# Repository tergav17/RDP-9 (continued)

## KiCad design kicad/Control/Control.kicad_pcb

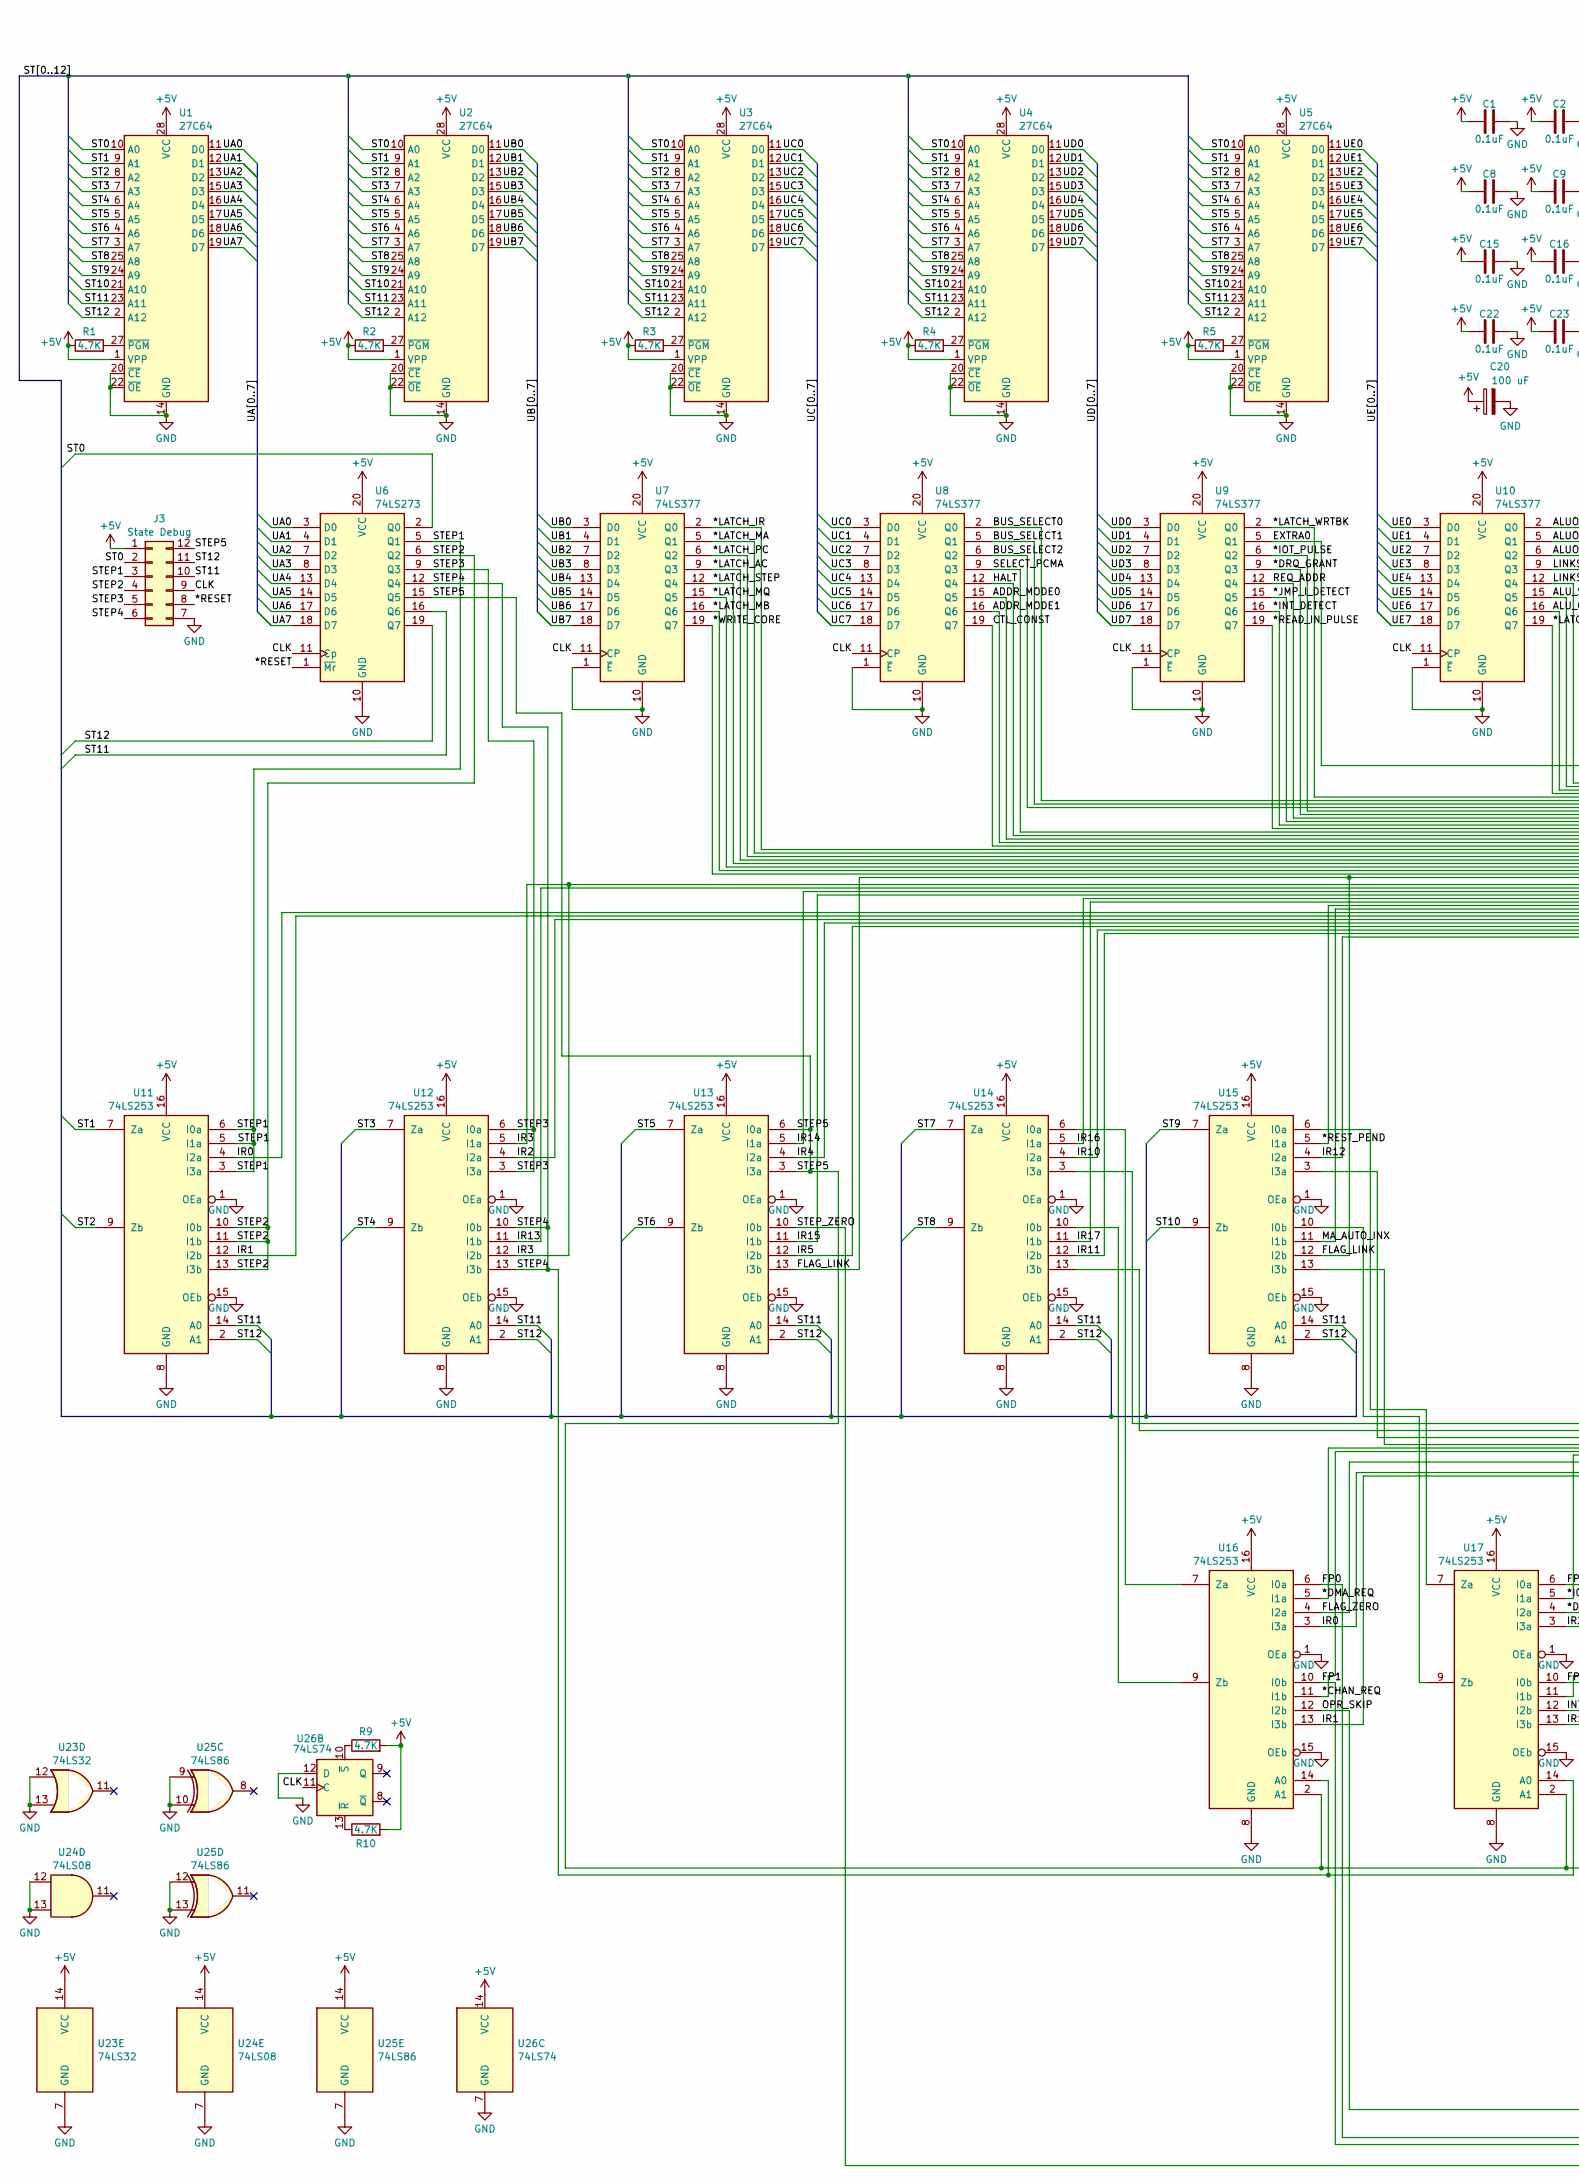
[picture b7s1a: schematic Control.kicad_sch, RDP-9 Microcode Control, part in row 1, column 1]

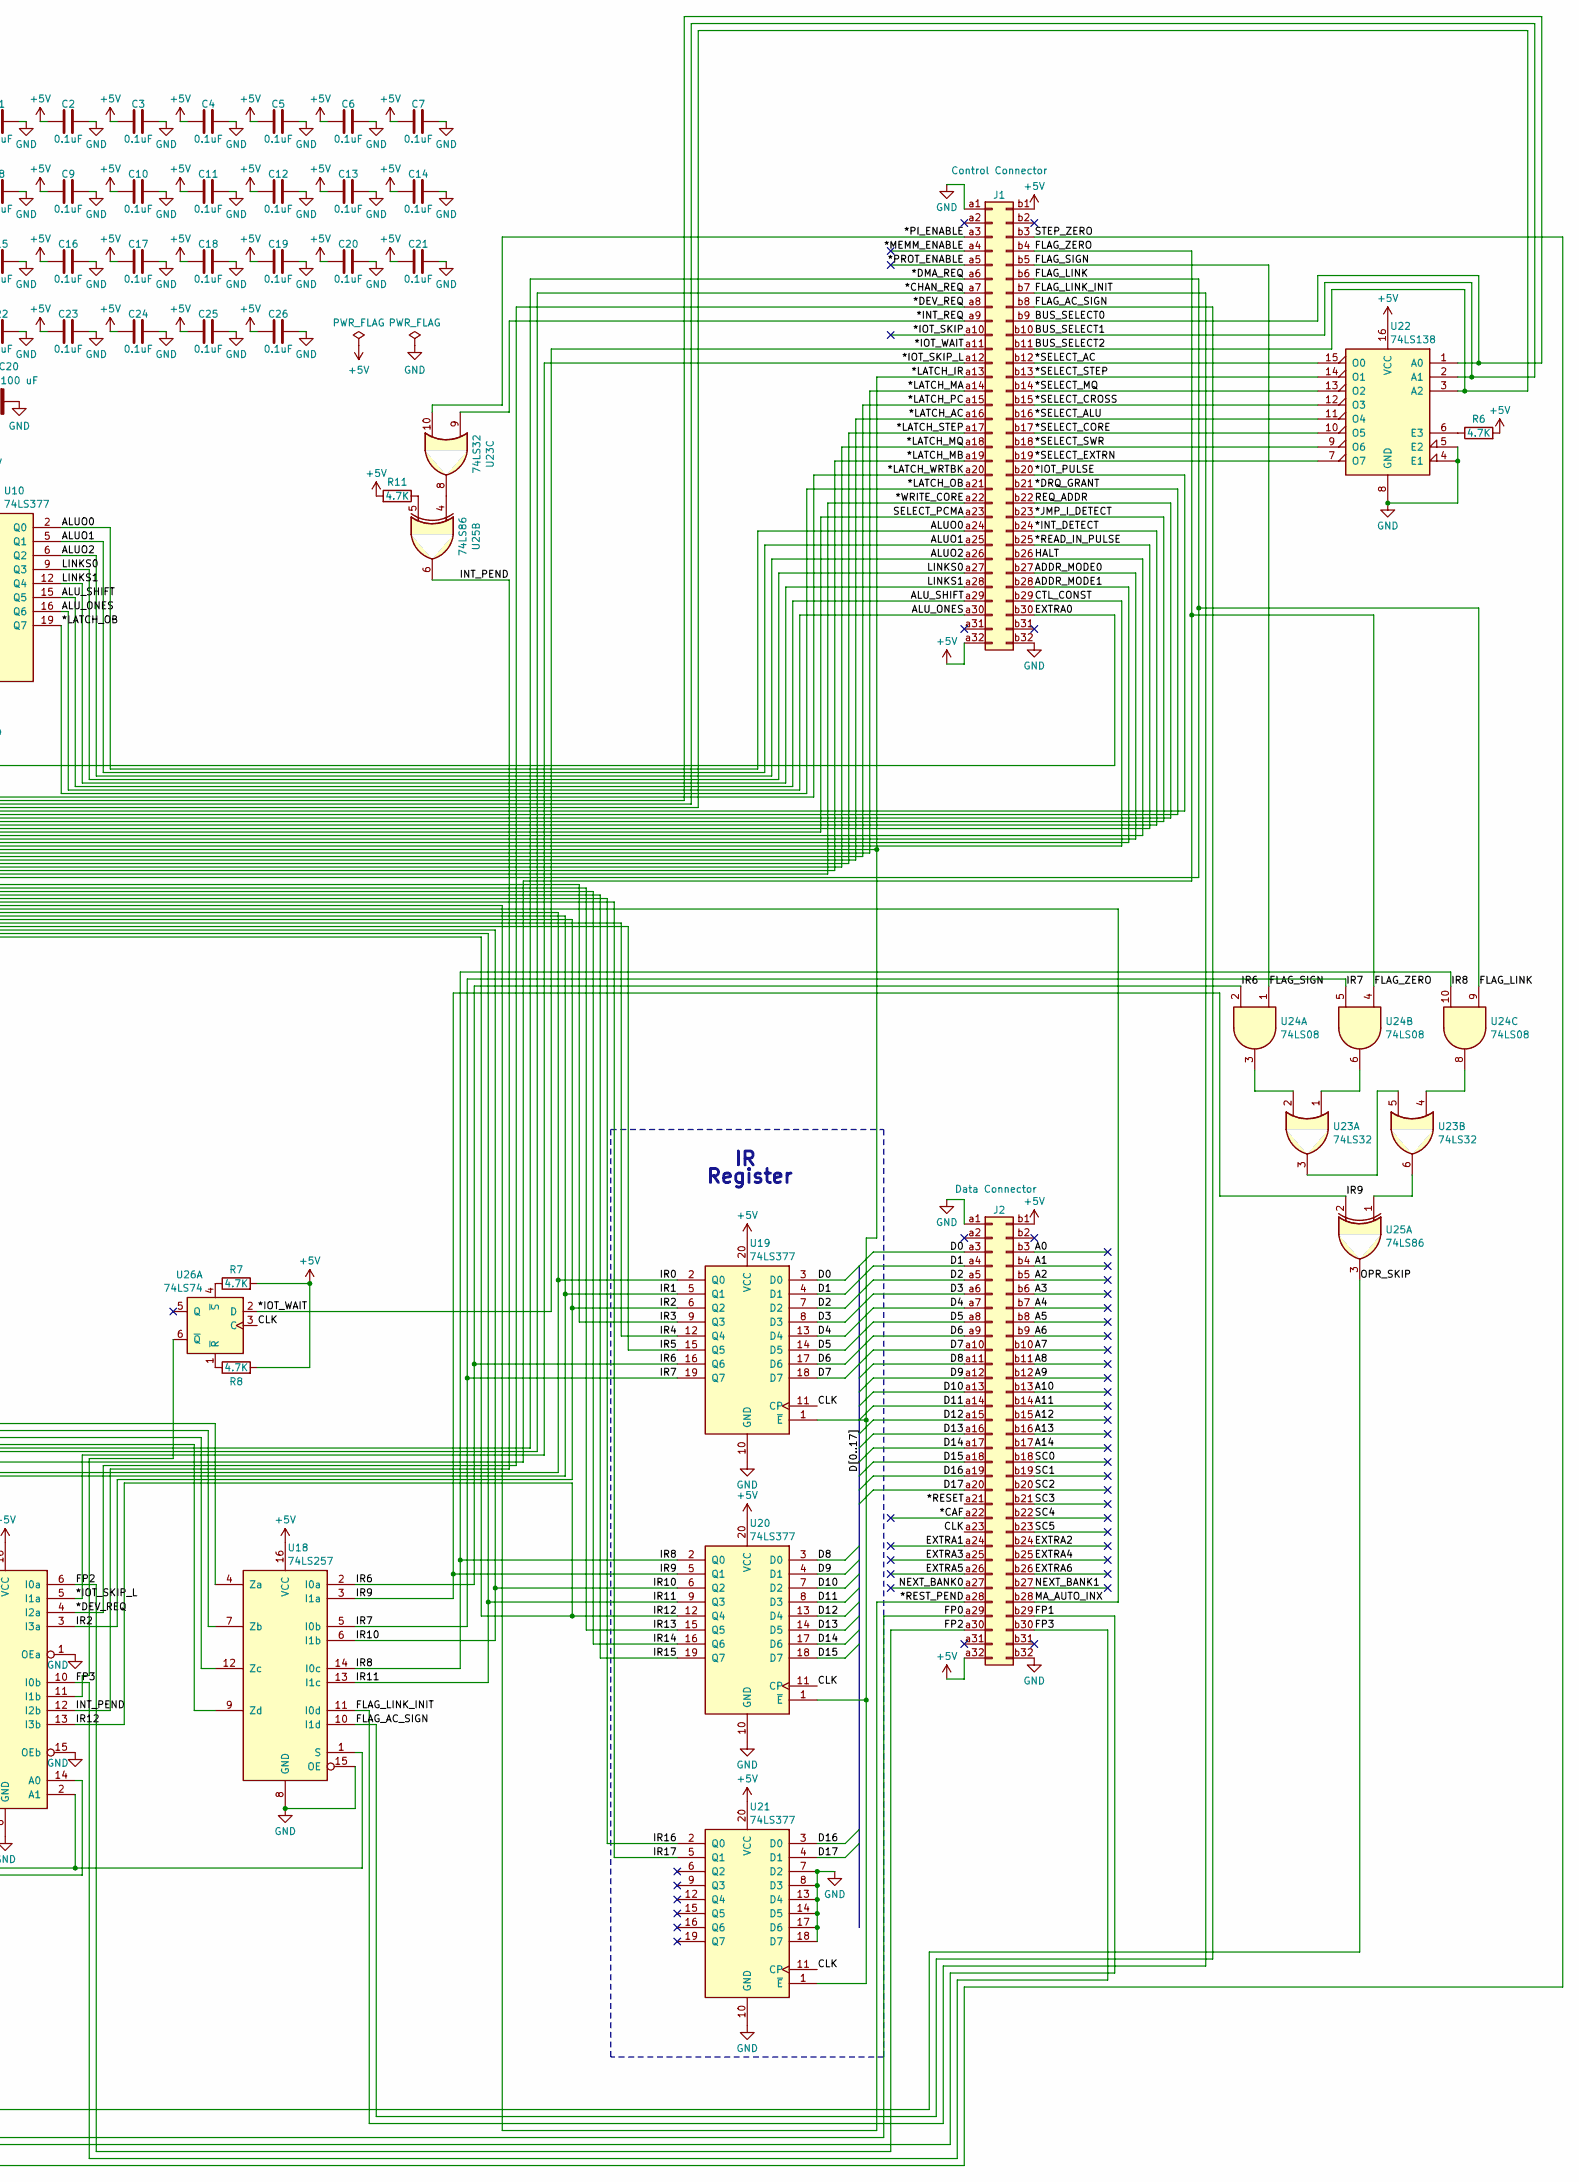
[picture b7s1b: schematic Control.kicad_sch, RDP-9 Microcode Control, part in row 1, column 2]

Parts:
C1, C2, C3, C4, C5, C6, C7, C8, C9, C10, C11, C12, C13, C14, C15, C16, C17, C18, C19, C21, C22, C23, C24, C25, C26: 0.1uF; C_Disc_D5.0mm_W2.5mm_P5.00mm
C20: 100 uF; CP_Radial_D6.3mm_P2.50mm
J1: Control Connector; DIN41612_B_2x32_Male_Horizontal_THT
J2: Data Connector; DIN41612_B_2x32_Male_Horizontal_THT
J3: State Debug; IDC-Header_2x06_P2.54mm_Horizontal
R1, R2, R3, R4, R5, R6, R7, R8, R9, R10, R11: 4.7K; R_Axial_DIN0207_L6.3mm_D2.5mm_P7.62mm_Horizontal
U1, U2, U3, U4, U5: 27C64; DIP-28_W15.24mm
U6: 74LS273; DIP-20_W7.62mm
U7, U8, U9, U10, U19, U20, U21: 74LS377; DIP-20_W7.62mm
U11, U12, U13, U14, U15, U16, U17: 74LS253; DIP-16_W7.62mm
U18: 74LS257; DIP-16_W7.62mm
U22: 74LS138; DIP-16_W7.62mm
U23: 74LS32; DIP-14_W7.62mm
U24: 74LS08; DIP-14_W7.62mm
U25: 74LS86; DIP-14_W7.62mm
U26: 74LS74; DIP-14_W7.62mm

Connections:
+5V: C1.1, C2.1, C3.1, C4.1, C5.1, C6.1, C7.1, C8.1, C9.1, C10.1, C11.1, C12.1, C13.1, C14.1, C15.1, C16.1, C17.1, C18.1, C19.1, C20.1, C21.1, C22.1, C23.1, C24.1, C25.1, C26.1, J1.a32, J1.b1, J2.a32, J2.b1, J3.1, R1.1, R2.1, R3.1, R4.1, R5.1, R6.2, R7.2, R8.2, R9.2, R10.2, R11.2, U1.1 (VPP), U1.28 (VCC), U2.1 (VPP), U2.28 (VCC), U3.1 (VPP), U3.28 (VCC), U4.1 (VPP), U4.28 (VCC), U5.1 (VPP), U5.28 (VCC), U6.20 (VCC), U7.20 (VCC), U8.20 (VCC), U9.20 (VCC), U10.20 (VCC), U11.16 (VCC), U12.16 (VCC), U13.16 (VCC), U14.16 (VCC), U15.16 (VCC), U16.16 (VCC), U17.16 (VCC), U18.16 (VCC), U19.20 (VCC), U20.20 (VCC), U21.20 (VCC), U22.16 (VCC), U23.14 (VCC), U24.14 (VCC), U25.14 (VCC), U26.14 (VCC); also elsewhere on the board
/*CAF: J2.a22
/*CHAN_REQ: J1.a7, U16.11 (I1b)
/*DEV_REQ: J1.a8, U17.4 (I2a)
/*DMA_REQ: J1.a6, U16.5 (I1a)
/*DRQ_GRANT: J1.b21, U9.9 (Q3)
/*INT_DETECT: J1.b24, U9.16 (Q6)
/*INT_REQ: J1.a9, U23.9
/*IOT_PULSE: J1.b20, U9.6 (Q2)
/*IOT_SKIP: J1.a10
/*IOT_SKIP_L: J1.a12, U17.5 (I1a)
/*IOT_WAIT: J1.a11, U26.2 (D)
/*JMP_I_DETECT: J1.b23, U9.15 (Q5)
/*LATCH_AC: J1.a16, U7.9 (Q3)
/*LATCH_IR: J1.a13, U7.2 (Q0), U19.1 (~E), U20.1 (~E), U21.1 (~E)
/*LATCH_MA: J1.a14, U7.5 (Q1)
/*LATCH_MB: J1.a19, U7.16 (Q6)
/*LATCH_MQ: J1.a18, U7.15 (Q5)
/*LATCH_OB: J1.a21, U10.19 (Q7)
/*LATCH_PC: J1.a15, U7.6 (Q2)
/*LATCH_STEP: J1.a17, U7.12 (Q4)
/*LATCH_WRTBK: J1.a20, U9.2 (Q0)
/*MEMM_ENABLE: J1.a4
/*PI_ENABLE: J1.a3, U23.10
/*PROT_ENABLE: J1.a5
/*READ_IN_PULSE: J1.b25, U9.19 (Q7)
/*RESET: J2.a21, J3.8, U6.1 (~Mr)
/*REST_PEND: J2.a28, U15.5 (I1a)
/*SELECT_AC: J1.b12, U22.15 (O0)
/*SELECT_ALU: J1.b16, U22.11 (O4)
/*SELECT_CORE: J1.b17, U22.10 (O5)
/*SELECT_CROSS: J1.b15, U22.12 (O3)
/*SELECT_EXTRN: J1.b19, U22.7 (O7)
/*SELECT_MQ: J1.b14, U22.13 (O2)
/*SELECT_STEP: J1.b13, U22.14 (O1)
/*SELECT_SWR: J1.b18, U22.9 (O6)
/*WRITE_CORE: J1.a22, U7.19 (Q7)
/A0: J2.b3
/A1: J2.b4
/A2: J2.b5
/A3: J2.b6
/A4: J2.b7
/A5: J2.b8
/A6: J2.b9
/A7: J2.b10
/A8: J2.b11
/A9: J2.b12
/A10: J2.b13
/A11: J2.b14
/A12: J2.b15
/A13: J2.b16
/A14: J2.b17
/ADDR_MODE0: J1.b27, U8.15 (Q5)
/ADDR_MODE1: J1.b28, U8.16 (Q6)
/ALUO0: J1.a24, U10.2 (Q0)
/ALUO1: J1.a25, U10.5 (Q1)
/ALUO2: J1.a26, U10.6 (Q2)
/ALU_ONES: J1.a30, U10.16 (Q6)
/ALU_SHIFT: J1.a29, U10.15 (Q5)
/BUS_SELECT0: J1.b9, U8.2 (Q0), U22.1 (A0)
/BUS_SELECT1: J1.b10, U8.5 (Q1), U22.2 (A1)
/BUS_SELECT2: J1.b11, U8.6 (Q2), U22.3 (A2)
/CLK: J2.a23, J3.9, U6.11 (Cp), U7.11 (CP), U8.11 (CP), U9.11 (CP), U10.11 (CP), U19.11 (CP), U20.11 (CP), U21.11 (CP), U26.3 (C), U26.11 (C)
/CTL_CONST: J1.b29, U8.19 (Q7)
/D0: J2.a3, U19.3 (D0)
/D1: J2.a4, U19.4 (D1)
/D2: J2.a5, U19.7 (D2)
/D3: J2.a6, U19.8 (D3)
/D4: J2.a7, U19.13 (D4)
/D5: J2.a8, U19.14 (D5)
/D6: J2.a9, U19.17 (D6)
/D7: J2.a10, U19.18 (D7)
/D8: J2.a11, U20.3 (D0)
/D9: J2.a12, U20.4 (D1)
/D10: J2.a13, U20.7 (D2)
/D11: J2.a14, U20.8 (D3)
/D12: J2.a15, U20.13 (D4)
/D13: J2.a16, U20.14 (D5)
/D14: J2.a17, U20.17 (D6)
/D15: J2.a18, U20.18 (D7)
/D16: J2.a19, U21.3 (D0)
/D17: J2.a20, U21.4 (D1)
/EXTRA0: J1.b30, U9.5 (Q1)
/EXTRA1: J2.a24
/EXTRA2: J2.b24
/EXTRA3: J2.a25
/EXTRA4: J2.b25
/EXTRA5: J2.a26
/EXTRA6: J2.b26
/FLAG_AC_SIGN: J1.b8, U18.10 (I1d)
/FLAG_LINK: J1.b6, U13.13 (I3b), U15.12 (I2b), U24.9
/FLAG_LINK_INIT: J1.b7, U18.11 (I0d)
/FLAG_SIGN: J1.b5, U24.1
/FLAG_ZERO: J1.b4, U16.4 (I2a), U24.4
/FP0: J2.a29, U16.6 (I0a)
/FP1: J2.b29, U16.10 (I0b)
/FP2: J2.a30, U17.6 (I0a)
/FP3: J2.b30, U17.10 (I0b)
/HALT: J1.b26, U8.12 (Q4)
/INT_PEND: U17.12 (I2b), U25.6
/IR0: U11.4 (I2a), U16.3 (I3a), U19.2 (Q0)
/IR1: U11.12 (I2b), U16.13 (I3b), U19.5 (Q1)
/IR2: U12.4 (I2a), U17.3 (I3a), U19.6 (Q2)
/IR3: U12.5 (I1a), U12.12 (I2b), U19.9 (Q3)
/IR4: U13.4 (I2a), U19.12 (Q4)
/IR5: U13.12 (I2b), U19.15 (Q5)
/IR6: U18.2 (I0a), U19.16 (Q6), U24.2
/IR7: U18.5 (I0b), U19.19 (Q7), U24.5
/IR8: U18.14 (I0c), U20.2 (Q0), U24.10
/IR9: U18.3 (I1a), U20.5 (Q1), U25.2
/IR10: U14.4 (I2a), U18.6 (I1b), U20.6 (Q2)
/IR11: U14.12 (I2b), U18.13 (I1c), U20.9 (Q3)
/IR12: U15.4 (I2a), U17.13 (I3b), U20.12 (Q4)
/IR13: U12.11 (I1b), U20.15 (Q5)
/IR14: U13.5 (I1a), U20.16 (Q6)
/IR15: U13.11 (I1b), U20.19 (Q7)
/IR16: U14.5 (I1a), U21.2 (Q0)
/IR17: U14.11 (I1b), U21.5 (Q1)
/LINKS0: J1.a27, U10.9 (Q3)
/LINKS1: J1.a28, U10.12 (Q4)
/MA_AUTO_INX: J2.b28, U15.11 (I1b)
/NEXT_BANK0: J2.a27
/NEXT_BANK1: J2.b27
/OPR_SKIP: U16.12 (I2b), U25.3
/REQ_ADDR: J1.b22, U9.12 (Q4)
/SC0: J2.b18
/SC1: J2.b19
/SC2: J2.b20
/SC3: J2.b21
/SC4: J2.b22
/SC5: J2.b23
/SELECT_PCMA: J1.a23, U8.9 (Q3)
/ST0: J3.2, U1.10 (A0), U2.10 (A0), U3.10 (A0), U4.10 (A0), U5.10 (A0), U6.2 (Q0)
/ST1: U1.9 (A1), U2.9 (A1), U3.9 (A1), U4.9 (A1), U5.9 (A1), U11.7 (Za)
/ST2: U1.8 (A2), U2.8 (A2), U3.8 (A2), U4.8 (A2), U5.8 (A2), U11.9 (Zb)
/ST3: U1.7 (A3), U2.7 (A3), U3.7 (A3), U4.7 (A3), U5.7 (A3), U12.7 (Za)
/ST4: U1.6 (A4), U2.6 (A4), U3.6 (A4), U4.6 (A4), U5.6 (A4), U12.9 (Zb)
/ST5: U1.5 (A5), U2.5 (A5), U3.5 (A5), U4.5 (A5), U5.5 (A5), U13.7 (Za)
/ST6: U1.4 (A6), U2.4 (A6), U3.4 (A6), U4.4 (A6), U5.4 (A6), U13.9 (Zb)
/ST7: U1.3 (A7), U2.3 (A7), U3.3 (A7), U4.3 (A7), U5.3 (A7), U14.7 (Za)
/ST8: U1.25 (A8), U2.25 (A8), U3.25 (A8), U4.25 (A8), U5.25 (A8), U14.9 (Zb)
/ST9: U1.24 (A9), U2.24 (A9), U3.24 (A9), U4.24 (A9), U5.24 (A9), U15.7 (Za)
/ST10: U1.21 (A10), U2.21 (A10), U3.21 (A10), U4.21 (A10), U5.21 (A10), U15.9 (Zb)
/ST11: J3.10, U1.23 (A11), U2.23 (A11), U3.23 (A11), U4.23 (A11), U5.23 (A11), U6.16 (Q6), U11.14 (A0), U12.14 (A0), U13.14 (A0), U14.14 (A0), U15.14 (A0)
/ST12: J3.11, U1.2 (A12), U2.2 (A12), U3.2 (A12), U4.2 (A12), U5.2 (A12), U6.19 (Q7), U11.2 (A1), U12.2 (A1), U13.2 (A1), U14.2 (A1), U15.2 (A1)
/STEP1: J3.3, U6.5 (Q1), U11.3 (I3a), U11.5 (I1a), U11.6 (I0a)
/STEP2: J3.4, U6.6 (Q2), U11.10 (I0b), U11.11 (I1b), U11.13 (I3b)
/STEP3: J3.5, U6.9 (Q3), U12.3 (I3a), U12.6 (I0a)
/STEP4: J3.6, U6.12 (Q4), U12.10 (I0b), U12.13 (I3b), U16.14 (A0), U17.14 (A0)
/STEP5: J3.12, U6.15 (Q5), U13.3 (I3a), U13.6 (I0a), U16.2 (A1), U17.2 (A1), U18.1 (S)
/STEP_ZERO: J1.b3, U13.10 (I0b)
/UA0: U1.11 (D0), U6.3 (D0)
/UA1: U1.12 (D1), U6.4 (D1)
/UA2: U1.13 (D2), U6.7 (D2)
/UA3: U1.15 (D3), U6.8 (D3)
/UA4: U1.16 (D4), U6.13 (D4)
/UA5: U1.17 (D5), U6.14 (D5)
/UA6: U1.18 (D6), U6.17 (D6)
/UA7: U1.19 (D7), U6.18 (D7)
/UB0: U2.11 (D0), U7.3 (D0)
/UB1: U2.12 (D1), U7.4 (D1)
/UB2: U2.13 (D2), U7.7 (D2)
/UB3: U2.15 (D3), U7.8 (D3)
/UB4: U2.16 (D4), U7.13 (D4)
/UB5: U2.17 (D5), U7.14 (D5)
/UB6: U2.18 (D6), U7.17 (D6)
/UB7: U2.19 (D7), U7.18 (D7)
/UC0: U3.11 (D0), U8.3 (D0)
/UC1: U3.12 (D1), U8.4 (D1)
/UC2: U3.13 (D2), U8.7 (D2)
/UC3: U3.15 (D3), U8.8 (D3)
/UC4: U3.16 (D4), U8.13 (D4)
/UC5: U3.17 (D5), U8.14 (D5)
/UC6: U3.18 (D6), U8.17 (D6)
/UC7: U3.19 (D7), U8.18 (D7)
/UD0: U4.11 (D0), U9.3 (D0)
/UD1: U4.12 (D1), U9.4 (D1)
/UD2: U4.13 (D2), U9.7 (D2)
/UD3: U4.15 (D3), U9.8 (D3)
/UD4: U4.16 (D4), U9.13 (D4)
/UD5: U4.17 (D5), U9.14 (D5)
/UD6: U4.18 (D6), U9.17 (D6)
/UD7: U4.19 (D7), U9.18 (D7)
/UE0: U5.11 (D0), U10.3 (D0)
/UE1: U5.12 (D1), U10.4 (D1)
/UE2: U5.13 (D2), U10.7 (D2)
/UE3: U5.15 (D3), U10.8 (D3)
/UE4: U5.16 (D4), U10.13 (D4)
/UE5: U5.17 (D5), U10.14 (D5)
/UE6: U5.18 (D6), U10.17 (D6)
/UE7: U5.19 (D7), U10.18 (D7)
GND: C1.2, C2.2, C3.2, C4.2, C5.2, C6.2, C7.2, C8.2, C9.2, C10.2, C11.2, C12.2, C13.2, C14.2, C15.2, C16.2, C17.2, C18.2, C19.2, C20.2, C21.2, C22.2, C23.2, C24.2, C25.2, C26.2, J1.a1, J1.b32, J2.a1, J2.b32, J3.7, U1.14 (GND), U1.20 (~CE), U1.22 (~OE), U2.14 (GND), U2.20 (~CE), U2.22 (~OE), U3.14 (GND), U3.20 (~CE), U3.22 (~OE), U4.14 (GND), U4.20 (~CE), U4.22 (~OE), U5.14 (GND), U5.20 (~CE), U5.22 (~OE), U6.10 (GND), U7.1 (~E), U7.10 (GND), U8.1 (~E), U8.10 (GND), U9.1 (~E), U9.10 (GND), U10.1 (~E), U10.10 (GND), U11.1 (OEa), U11.8 (GND), U11.15 (OEb), U12.1 (OEa), U12.8 (GND), U12.15 (OEb), U13.1 (OEa), U13.8 (GND), U13.15 (OEb), U14.1 (OEa), U14.8 (GND), U14.15 (OEb), U15.1 (OEa), U15.8 (GND), U15.15 (OEb), U16.1 (OEa), U16.8 (GND), U16.15 (OEb), U17.1 (OEa), U17.8 (GND), U17.15 (OEb), U18.8 (GND), U18.15 (OE), U19.10 (GND), U20.10 (GND), U21.7 (D2), U21.8 (D3), U21.10 (GND), U21.13 (D4), U21.14 (D5), U21.17 (D6), U21.18 (D7), U22.4 (E1), U22.5 (E2), U22.8 (GND), U23.7 (GND), U23.12, U23.13, U24.7 (GND), U24.12, U24.13, U25.7 (GND), U25.9, U25.10, U25.12, U25.13, U26.7 (GND), U26.12 (D); also elsewhere on the board
unnamed: R11.1, U25.5
unnamed: R1.2, U1.27 (~PGM)
unnamed: R2.2, U2.27 (~PGM)
unnamed: R3.2, U3.27 (~PGM)
unnamed: R4.2, U4.27 (~PGM)
unnamed: R5.2, U5.27 (~PGM)
unnamed: U14.6 (I0a), U16.7 (Za)
unnamed: U14.10 (I0b), U16.9 (Zb)
unnamed: U14.3 (I3a), U18.4 (Za)
unnamed: U14.13 (I3b), U18.7 (Zb)
unnamed: U15.6 (I0a), U17.7 (Za)
unnamed: U15.10 (I0b), U17.9 (Zb)
unnamed: U15.3 (I3a), U18.12 (Zc)
unnamed: U15.13 (I3b), U18.9 (Zd)
unnamed: U17.11 (I1b), U26.6 (~Q)
unnamed: R6.1, U22.6 (E3)
unnamed: U23.1, U24.6
unnamed: U23.2, U24.3
unnamed: U23.3, U23.5
unnamed: U23.4, U24.8
unnamed: U23.6, U25.1
unnamed: U23.8, U25.4
unnamed: R8.1, U26.1 (~R)
unnamed: R7.1, U26.4 (~S)
unnamed: R10.1, U26.13 (~R)
unnamed: R9.1, U26.10 (~S)

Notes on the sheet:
Register

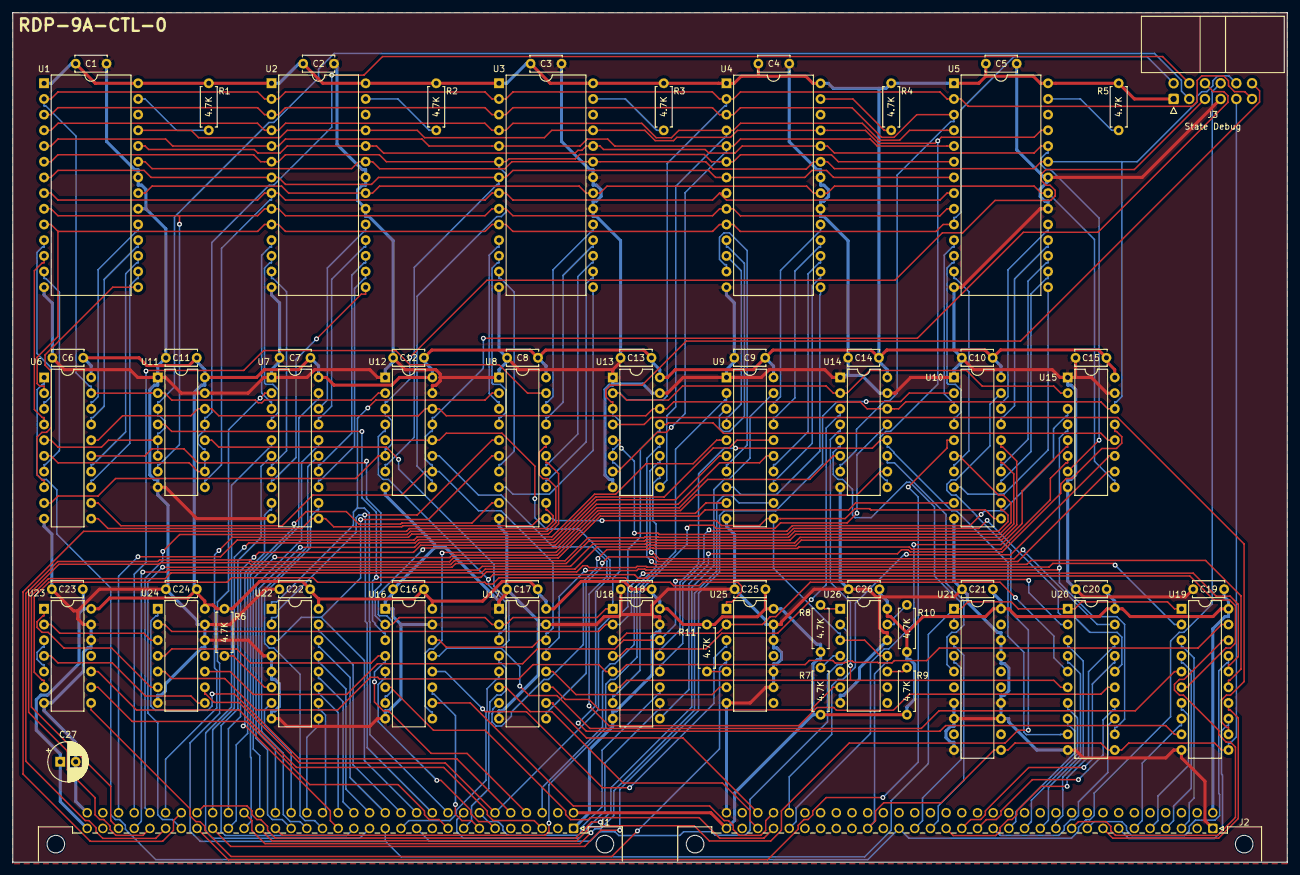
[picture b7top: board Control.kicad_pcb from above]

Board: 2 copper layers, 206.4 x 137.5 mm, 67 parts (0 on the bottom side), 185 nets.

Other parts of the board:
C27: 100 uF; CP_Radial_D6.3mm_P2.50mm

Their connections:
+5V: C27.1; also elsewhere on the board
GND: C27.2; also elsewhere on the board

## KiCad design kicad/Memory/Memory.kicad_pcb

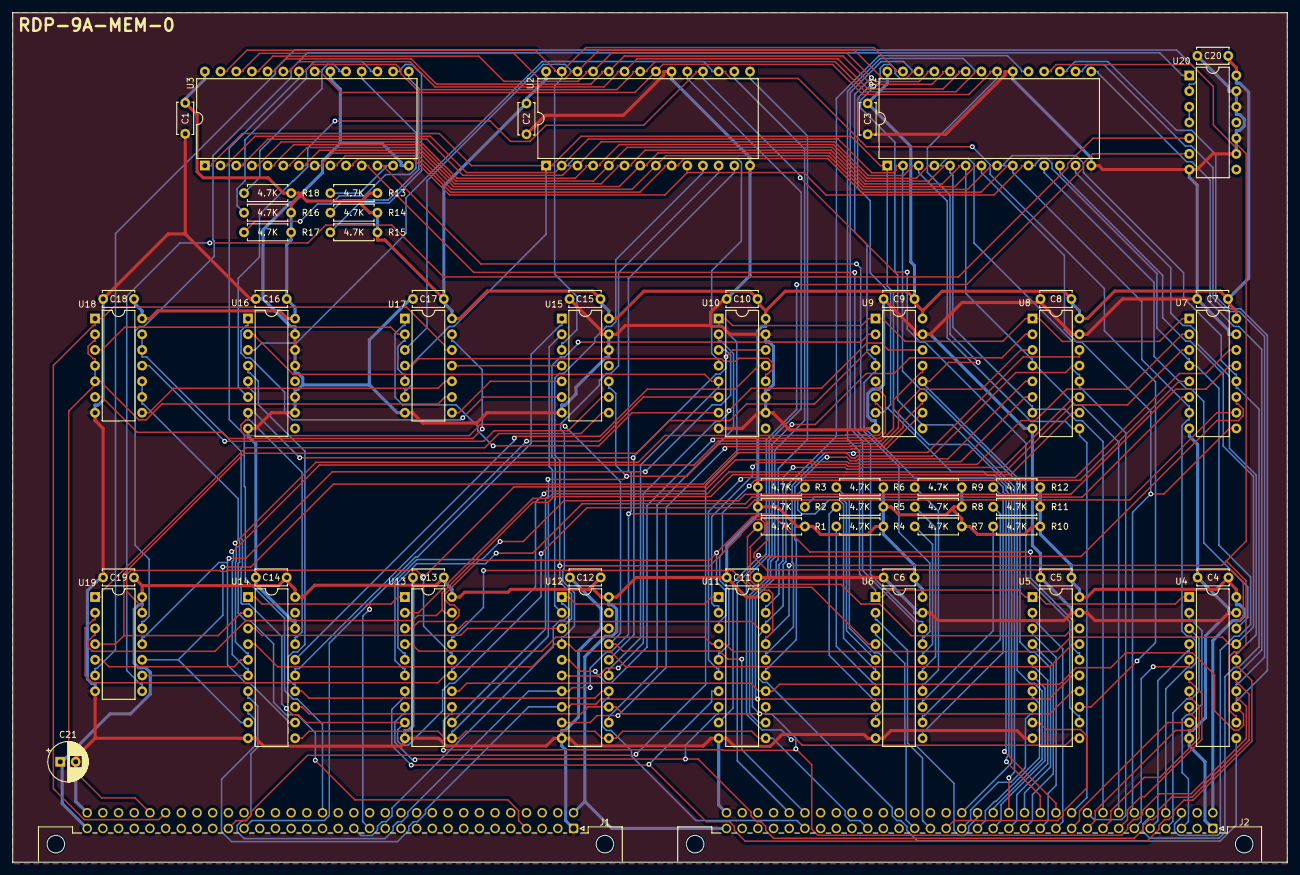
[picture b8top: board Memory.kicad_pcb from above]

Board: 2 copper layers, 206.4 x 137.5 mm, 61 parts (0 on the bottom side), 128 nets.

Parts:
C1, C2, C3, C4, C5, C6, C7, C8, C9, C10, C11, C12, C13, C14, C15, C16, C17, C18, C19, C20: 0.1uF; C_Disc_D5.0mm_W2.5mm_P5.00mm
C21: 100 uF; CP_Radial_D6.3mm_P2.50mm
J1: Control Connector; DIN41612_B_2x32_Male_Horizontal_THT
J2: Data Connector; DIN41612_B_2x32_Male_Horizontal_THT
R1, R2, R3, R4, R5, R6, R7, R8, R9, R10, R11, R12, R13, R14, R15, R16, R17, R18: 4.7K; R_Axial_DIN0207_L6.3mm_D2.5mm_P7.62mm_Horizontal
U1, U2, U3: CY62256-70PC; DIP-28_W15.24mm
U4, U5, U6: 74LS245; DIP-20_W7.62mm
U7, U8, U9, U10, U16: 74LS257; DIP-16_W7.62mm
U11, U12, U13, U14: 74LS377; DIP-20_W7.62mm
U15: 74LS32; DIP-14_W7.62mm
U17, U20: 74LS08; DIP-14_W7.62mm
U18: 74LS00; DIP-14_W7.62mm
U19: 74LS27; DIP-14_W7.62mm

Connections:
+5V: C1.1, C2.1, C3.1, C4.1, C5.1, C6.1, C7.1, C8.1, C9.1, C10.1, C11.1, C12.1, C13.1, C14.1, C15.1, C16.1, C17.1, C18.1, C19.1, C20.1, C21.1, J1.a32, J1.b1, J2.a32, J2.b1, R1.2, R2.2, R3.2, R4.2, R5.2, R6.2, R7.2, R8.2, R9.2, R10.2, R11.2, R12.2, R13.2, R14.2, R15.2, R16.2, R17.2, R18.2, U1.28 (VCC), U2.28 (VCC), U3.28 (VCC), U4.20 (VCC), U5.20 (VCC), U6.20 (VCC), U7.16 (VCC), U8.16 (VCC), U9.16 (VCC), U10.16 (VCC), U11.20 (VCC), U12.20 (VCC), U13.20 (VCC), U14.20 (VCC), U15.14 (VCC), U16.16 (VCC), U17.14 (VCC), U18.14 (VCC), U19.14 (VCC), U20.14 (VCC)
/*LATCH_MA: J1.a14, U13.1 (~E), U14.1 (~E)
/*LATCH_PC: J1.a15, U11.1 (~E), U12.1 (~E)
/*MEMM_ENABLE: J1.a4, U18.9, U18.10
/*SELECT_CORE: J1.b17, U1.22 (~OE), U2.22 (~OE), U3.22 (~OE), U4.1 (A->B), U5.1 (A->B), U6.1 (A->B)
/*WRITE_CORE: J1.a22, U15.1
/A0: J2.b3, U1.10 (A0), U2.10 (A0), U3.10 (A0), U7.4 (Za)
/A1: J2.b4, U1.9 (A1), U2.9 (A1), U3.9 (A1), U7.7 (Zb)
/A2: J2.b5, U1.8 (A2), U2.8 (A2), U3.8 (A2), U7.12 (Zc)
/A3: J2.b6, U1.7 (A3), U2.7 (A3), U3.7 (A3), U7.9 (Zd)
/A4: J2.b7, U1.6 (A4), U2.6 (A4), U3.6 (A4), U8.4 (Za)
/A5: J2.b8, U1.5 (A5), U2.5 (A5), U3.5 (A5), U8.7 (Zb)
/A6: J2.b9, U1.4 (A6), U2.4 (A6), U3.4 (A6), U8.12 (Zc)
/A7: J2.b10, U1.3 (A7), U2.3 (A7), U3.3 (A7), U8.9 (Zd)
/A8: J2.b11, U1.25 (A8), U2.25 (A8), U3.25 (A8), U9.4 (Za)
/A9: J2.b12, U1.24 (A9), U2.24 (A9), U3.24 (A9), U9.7 (Zb)
/A10: J2.b13, U1.21 (A10), U2.21 (A10), U3.21 (A10), U9.12 (Zc)
/A11: J2.b14, U1.23 (A11), U2.23 (A11), U3.23 (A11), U9.9 (Zd)
/A12: J2.b15, U1.2 (A12), U2.2 (A12), U3.2 (A12), U10.4 (Za)
/A13: J2.b16, U1.26 (A13), U2.26 (A13), U3.26 (A13), U17.3
/A14: J2.b17, U1.1 (A14), U2.1 (A14), U3.1 (A14), U17.6
/ADDR_MODE0: J1.b27, U17.12, U18.1
/ADDR_MODE1: J1.b28, U17.9, U18.2, U18.4, U18.5
/CLK: J2.a23, U11.11 (CP), U12.11 (CP), U13.11 (CP), U14.11 (CP), U15.2
/D0: J2.a3, U4.2 (A0)
/D1: J2.a4, U4.3 (A1)
/D2: J2.a5, U4.4 (A2)
/D3: J2.a6, U4.5 (A3)
/D4: J2.a7, U4.6 (A4)
/D5: J2.a8, U4.7 (A5)
/D6: J2.a9, U4.8 (A6)
/D7: J2.a10, U4.9 (A7)
/D8: J2.a11, U5.2 (A0)
/D9: J2.a12, U5.3 (A1)
/D10: J2.a13, U5.4 (A2)
/D11: J2.a14, U5.5 (A3)
/D12: J2.a15, U5.6 (A4)
/D13: J2.a16, U5.7 (A5)
/D14: J2.a17, U5.8 (A6)
/D15: J2.a18, U5.9 (A7)
/D16: J2.a19, U6.2 (A0)
/D17: J2.a20, U6.3 (A1)
/EXTEND: U15.6, U16.1 (S)
/M0: U1.11 (Q0), U4.18 (B0), U11.3 (D0), U13.3 (D0)
/M1: U1.12 (Q1), U4.17 (B1), U11.4 (D1), U13.4 (D1)
/M2: U1.13 (Q2), U4.16 (B2), U11.7 (D2), U13.7 (D2)
/M3: U1.15 (Q3), U4.15 (B3), U11.8 (D3), U13.8 (D3)
/M4: U1.16 (Q4), U4.14 (B4), U11.13 (D4), U13.13 (D4)
/M5: U1.17 (Q5), U4.13 (B5), U11.14 (D5), U13.14 (D5)
/M6: U1.18 (Q6), U4.12 (B6), U11.17 (D6), U13.17 (D6)
/M7: U1.19 (Q7), U4.11 (B7), U11.18 (D7), U13.18 (D7)
/M8: U2.11 (Q0), U5.18 (B0), U12.3 (D0), U14.3 (D0)
/M9: U2.12 (Q1), U5.17 (B1), U12.4 (D1), U14.4 (D1)
/M10: U2.13 (Q2), U5.16 (B2), U12.7 (D2), U14.7 (D2)
/M11: U2.15 (Q3), U5.15 (B3), U12.8 (D3), U14.8 (D3)
/M12: U2.16 (Q4), U5.14 (B4), U12.13 (D4), U14.13 (D4)
/M13: U2.17 (Q5), U5.13 (B5), U16.3 (I1a)
/M14: U2.18 (Q6), U5.12 (B6), U16.6 (I1b)
/M15: U2.19 (Q7), U5.11 (B7)
/M16: U3.11 (Q0), U6.18 (B0)
/M17: U3.12 (Q1), U6.17 (B1)
/MA0: U7.3 (I1a), U13.2 (Q0)
/MA1: U7.6 (I1b), U13.5 (Q1)
/MA2: U7.13 (I1c), U13.6 (Q2)
/MA3: U7.10 (I1d), U13.9 (Q3), U18.12, U18.13
/MA4: U8.3 (I1a), U13.12 (Q4), U15.10
/MA5: U8.6 (I1b), U13.15 (Q5), U19.2
/MA6: U8.13 (I1c), U13.16 (Q6), U19.13
/MA7: U8.10 (I1d), U13.19 (Q7), U19.3
/MA8: U9.3 (I1a), U14.2 (Q0), U19.4
/MA9: U9.6 (I1b), U14.5 (Q1), U19.5
/MA10: U9.13 (I1c), U14.6 (Q2), U19.9
/MA11: U9.10 (I1d), U14.9 (Q3), U19.10
/MA12: U10.3 (I1a), U14.12 (Q4), U19.11
/MA13: U10.6 (I1b), U14.15 (Q5)
/MA14: U10.13 (I1c), U14.16 (Q6)
/MA_AUTO_INX: J2.b28, U20.6
/NEXT_BANK0: J2.a27, U12.14 (D5), U14.14 (D5), U16.4 (Za)
/NEXT_BANK1: J2.b27, U12.17 (D6), U14.17 (D6), U16.7 (Zb)
/PC0: U7.2 (I0a), U11.2 (Q0)
/PC1: U7.5 (I0b), U11.5 (Q1)
/PC2: U7.14 (I0c), U11.6 (Q2)
/PC3: U7.11 (I0d), U11.9 (Q3)
/PC4: U8.2 (I0a), U11.12 (Q4)
/PC5: U8.5 (I0b), U11.15 (Q5)
/PC6: U8.14 (I0c), U11.16 (Q6)
/PC7: U8.11 (I0d), U11.19 (Q7)
/PC8: U9.2 (I0a), U12.2 (Q0)
/PC9: U9.5 (I0b), U12.5 (Q1)
/PC10: U9.14 (I0c), U12.6 (Q2)
/PC11: U9.11 (I0d), U12.9 (Q3)
/PC12: U10.2 (I0a), U12.12 (Q4)
/PC13: U10.5 (I0b), U12.15 (Q5), U16.2 (I0a)
/PC14: U10.14 (I0c), U12.16 (Q6), U16.5 (I0b)
/SELECT_PCMA: J1.a23, U7.1 (S), U8.1 (S), U9.1 (S), U10.1 (S)
/T0: R1.1, U6.4 (A2)
/T1: R2.1, U6.5 (A3)
/T2: R3.1, U6.6 (A4)
/T3: R4.1, U6.7 (A5)
/T4: R5.1, U6.8 (A6)
/T5: R6.1, U6.9 (A7)
/T6: R7.1, U6.16 (B2)
/T7: R8.1, U6.15 (B3)
/T8: R9.1, U6.14 (B4)
/T9: R10.1, U6.13 (B5)
/T10: R11.1, U6.12 (B6)
/T11: R12.1, U6.11 (B7)
/T12: R13.1, U3.13 (Q2)
/T13: R14.1, U3.15 (Q3)
/T14: R15.1, U3.16 (Q4)
/T15: R16.1, U3.17 (Q5)
/T16: R17.1, U3.18 (Q6)
/T17: R18.1, U3.19 (Q7)
GND: C1.2, C2.2, C3.2, C4.2, C5.2, C6.2, C7.2, C8.2, C9.2, C10.2, C11.2, C12.2, C13.2, C14.2, C15.2, C16.2, C17.2, C18.2, C19.2, C20.2, C21.2, J1.a1, J1.b32, J2.a1, J2.b32, U1.14 (GND), U1.20 (~CS), U2.14 (GND), U2.20 (~CS), U3.14 (GND), U3.20 (~CS), U4.10 (GND), U4.19 (CE), U5.10 (GND), U5.19 (CE), U6.10 (GND), U6.19 (CE), U7.8 (GND), U7.15 (OE), U8.8 (GND), U8.15 (OE), U9.8 (GND), U9.15 (OE), U10.8 (GND), U10.10 (I1d), U10.11 (I0d), U10.15 (OE), U11.10 (GND), U12.10 (GND), U12.18 (D7), U13.10 (GND), U14.10 (GND), U14.18 (D7), U15.7 (GND), U15.12, U15.13, U16.8 (GND), U16.10 (I1d), U16.11 (I0d), U16.13 (I1c), U16.14 (I0c), U16.15 (OE), U17.7 (GND), U18.7 (GND), U19.7 (GND), U20.7 (GND), U20.9, U20.10, U20.12, U20.13
unnamed: U1.27 (~WE), U2.27 (~WE), U3.27 (~WE), U15.3
unnamed: U10.7 (Zb), U17.1
unnamed: U10.12 (Zc), U17.4
unnamed: U15.4, U17.11
unnamed: U15.5, U17.8
unnamed: U15.8, U19.1
unnamed: U15.9, U18.11
unnamed: U17.2, U17.5, U18.3
unnamed: U17.10, U18.8
unnamed: U17.13, U18.6
unnamed: U19.6, U20.2
unnamed: U19.8, U20.5
unnamed: U19.12, U20.1
unnamed: U20.3, U20.4

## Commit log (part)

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2025-04-19 Fix project structure
2025-04-19 Remove dupped files
2025-04-20 Rework extended addressing logic
2025-04-21 Continue work on indirect addressing
2025-04-22 Add README.md
2025-04-23 Continued work on indirection
2025-04-24 Start work on CAL instruction
2025-04-24 Finish initial version of CAL
2025-04-25 Implement JMS instruction
2025-04-26 Implement DZM instruction
2025-04-26 Implement XOR instruction
2025-04-26 Implement ADD instruction
2025-04-26 Implement TAD instruction
2025-04-26 Implement XCT instruction
2025-04-27 Implement ISZ instruction
2025-04-28 Implement SAD instruction
2025-04-29 Fix SAD instruction
2025-04-30 Implement JMP instruction
2025-05-01 Begin implementation of OPR
2025-05-02 Implement LAW and continue work on OPR
2025-05-02 Fix STEP_ISR_OPR_SWR_OB
2025-05-03 Continue work on operate mode
2025-05-04 OPERATE mode microcode input
2025-05-05 Add switch register logic
2025-05-07 Add operate decoding
2025-05-08 Adjust step configuration for operate
2025-05-09 Continued work on OPR instruction
2025-05-10 Add link flag
2025-05-11 Continue work on stage 1 of OPR
2025-05-13 Implement shifter logic
2025-05-14 Add skip logic
2025-05-14 Continued work on operate
2025-05-15 Fix issues with OPR instruction
2025-05-17 Fix OPR skip conditions and add control switches
2025-05-17 Continue implementing front panel control
2025-05-19 Move front panel state to cpu state struct
2025-05-20 Implement state logic for front panel switches
2025-05-21 Lock switch update to 60hz timer
2025-05-22 Add button press logic
2025-05-23 Fix issue with redraw
2025-05-24 Add cpu state register
2025-05-24 Start implementing halt state
2025-05-24 Implement GOTO front panel operation
2025-05-24 Implement EXAM and EXAM NEXT
2025-05-24 Implement DEPT and DEPT NEXT
2025-05-24 Implement XCT front panel operation
2025-05-25 Fix bugs regarding halt state
2025-05-27 Fix tabbing
2025-05-28 Core dump
2025-05-29 Finish core dump
2025-05-30 Start work on paper tape mounting
2025-06-01 Add run tape button
2025-06-02 Start work on IOT instruction
2025-06-07 Change design to account for I/O coprocessor subsystem
2025-06-08 IO coprocessor status values
2025-06-09 Start working on processor side IOT logic
2025-06-10 Add more IOT coproc control signals
2025-06-11 Connect COPROC signals to microcode output
2025-06-12 Start coprocessor emulation code
2025-06-13 Continue work with IO coprocessor subsystem
2025-06-14 Decode bits from cpu state
2025-06-15 Set up coprocessor state machine
2025-09-12 Continue work on IOT instruction
2025-09-21 I/O state machine updates
2026-01-16 Minor bug fixes and write test program for paper tape read-in
2026-01-17 Work on MISC decode mode
2026-01-17 Fix up some of the IOT plumbing
2026-01-18 Integrate coprocessor and main CPU
2026-01-19 Implement PPT reader logic
2026-01-19 Add teleprinter support and fix load-in bug
2026-01-20 Fix assorted CPU bugs related to adder and CLL
2026-01-20 Add halt indiciator to front panel
2026-01-20 Mess around with the front panel and add bell to TTY
2026-01-21 Rewrite bus select logic to remove constant value
2026-01-22 Refactor addressing logic to remove ability to float bus
2026-01-23 Add breakpoint logic
2026-01-23 Fix "issue" with CAL instruction
2026-01-24 Fix XCT instruction
2026-01-25 Musings on interrupts
2026-01-25 Minor rework of fetch front panel logic
2026-01-27 Start plumbing IOT logic
2026-01-28 Remove I/O coprocessor
2026-01-29 Wire IO latching and prop to CPU
2026-01-29 Implement IOT microcode path
2026-01-30 Continue IOT work
2026-02-02 Debug issue with IOT skips
2026-02-02 Fix all sorts of bugs and add back TTY printer support
2026-02-03 Start work on device request logic
2026-02-04 Continue work on device request logic
2026-02-05 Break out device bus and data bus
2026-02-06 Add interrupt and memm flags to IO subsystem
2026-02-07 Switch back to unified device bus
2026-02-08 Update REAMDME
2026-02-09 Continue working on device request process
2026-02-10 Update I/O theory of operation
2026-02-11 Rework IOT logical inputs
2026-02-11 Rewrite IOT microcode to handle new redesign
2026-02-11 Migrate IO device logic to new IOT strategy
2026-02-12 Fix issues with new IOT procedure
2026-02-13 Continue work on DRQ logic
2026-02-14 Continue DRQ logic
2026-02-14 Finish initial sequence for DRQ process
2026-02-15 Start implementing DRQ priority logic in I/O subsystem
2026-02-16 Continue DRQ I/O logic
2026-02-17 Work on RTC implementation
2026-02-18 Wire in RTC to DRQ subsystem and debug
2026-02-18 Implement PIE flag
2026-02-19 Add interrupt pathway to microcode
2026-02-20 Start MEMM redesign
2026-02-21 Rework addressing selection scheme to allow for more modes
2026-02-22 Start updating indirection logic to handle indirect jump restores
2026-02-23 Finish implementation of restore logic
2026-02-24 Add CAF functionality
2026-02-24 Add IORS instruction
2026-02-25 Start working on DRQ design
2026-02-26 Finish design of READ-IN microcode pathway
2026-02-27 Start implementing READ-IN microcode
2026-02-27 Finish READ-IN microcode pathway
2026-03-01 Continue work on READ-IN
2026-03-02 Complete READ-IN logic
2026-03-03 Start implementing EAE
2026-03-04 Add TTY keyboard functionality
2026-03-05 Add MEMM IOTs
2026-03-06 Work on EMIR integration
2026-03-07 Continue work on EMIR logic
2026-03-08 Pull tooling and software into repo
2026-03-09 Refactor JMP opcode
2026-03-10 Change bit source to WRTBK
2026-03-11 Add debug statements
2026-03-12 Continue working on EXT memory test
2026-03-13 Debug issues with MEMM restore
2026-03-14 Continue DBR debugging work
2026-03-15 Hard-code RIM loader into memory
2026-03-16 Fix indirect wrtbk bug
2026-03-17 Enhance logging
2026-03-18 More debugging
2026-03-19 Continue debugging
2026-03-22 Fix EMIR bug
2026-03-23 Continue work on memory test
2026-03-24 Disable logging
2026-03-25 Continue work on extended memory tests
2026-03-26 Continue work on tests
2026-03-27 Continue testing
2026-03-28 Fix indirection issue
2026-03-30 Continue test work
2026-04-23 EAE setup work
2026-05-18 Complete MISC decode mode
2026-05-19 Fill out execution logic for EAE decode mode
2026-05-20 Continue implementing EAE setup pathway
2026-05-21 Update formatting
2026-05-22 Work on EAE MQ complement logic
2026-05-23 Continue work on EAE setup mode
2026-05-23 Complete EAE setup pathway
2026-05-23 Begin EAE setup debug effort
2026-05-23 Fix setup MQ manipulation pathway
2026-05-23 Add step counter to UI and fix more setup bugs
2026-05-24 More misc EAE setup bug fixes
2026-05-25 Start work on multiply logic pathway
2026-05-25 Modify multiply logic
2026-05-27 Continue multipler work
2026-05-27 Complete main multiply path
2026-05-28 Rework SC design and fix multiply bugs
2026-05-29 Start divide logic path
2026-05-30 Continue division work
2026-05-31 Continue work on divide logic
2026-05-31 Finish basic division pathway
2026-05-31 Fix EAE divide logic
2026-06-01 Implement EAE normalize instruction
2026-06-01 Fix normalize instruction
2026-06-01 Implement long right shift
2026-06-01 Implement LLS instruction
2026-06-01 Implement ALS instruction
2026-06-02 EAE debugathon
2026-06-03 Expand logging capabilities
2026-06-04 Continue bux fixing in EAE multiply
2026-06-06 Start work on RB emulation
2026-06-07 Continue work on RB emulation
2026-06-08 Continue work on RB emulation and fix DMA bug
2026-06-09 Modify the terminal to UNIX can run
2026-06-10 Start working on ALU schematic
2026-06-11 Simplify ALU carry out logic
2026-06-12 Continue ALU work
2026-06-13 Implement ALU arithmetic support logic
2026-06-13 Implement OB zero flag logic
2026-06-15 Start work on control board
2026-06-16 Start migrating over to DIN41612 connectors
2026-06-17 Add pinout document
2026-06-18 Continue pinout refactor work
2026-06-19 Switch out +12V pin
2026-06-20 Continue pinout work
2026-06-21 Continue pinout design
2026-06-22 Continue work on pinout
2026-06-23 Continue connector migration
2026-06-27 Fix electrical rule issues
2026-06-28 Rework CAF and continue control board schematic
2026-06-28 Finish control logic
2026-06-29 Start work on register file
2026-06-30 Continue work on register file
